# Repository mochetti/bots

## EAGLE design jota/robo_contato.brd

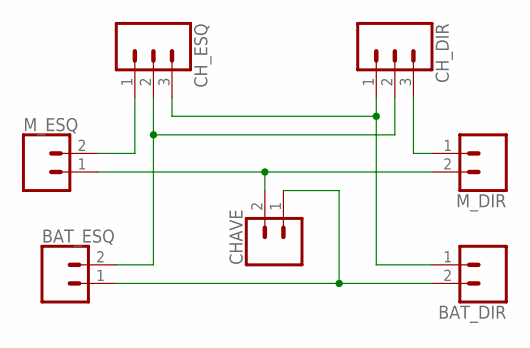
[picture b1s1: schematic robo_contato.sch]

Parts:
BAT_DIR: CONN_02; 1X02
BAT_ESQ: CONN_02; 1X02
CHAVE: CONN_02; 1X02
CH_DIR: CONN_03; 1X03
CH_ESQ: CONN_03; 1X03
M_DIR: CONN_02; 1X02
M_ESQ: CONN_02; 1X02

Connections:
unnamed: BAT_ESQ.2, CH_DIR.2, CH_ESQ.2
unnamed: CHAVE.2, M_DIR.2, M_ESQ.1
unnamed: BAT_DIR.1, CH_DIR.1, CH_ESQ.3
unnamed: CH_DIR.3, M_DIR.1
unnamed: CH_ESQ.1, M_ESQ.2
unnamed: BAT_DIR.2, BAT_ESQ.1, CHAVE.1

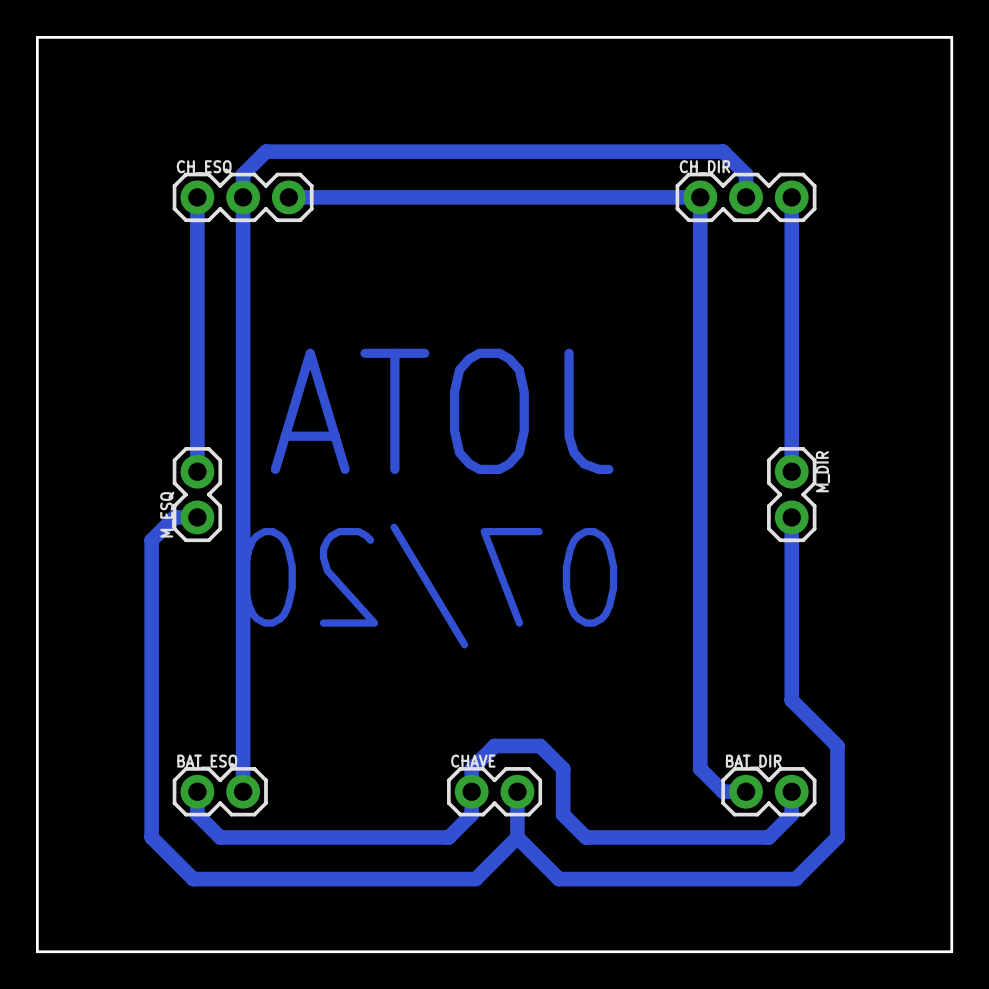
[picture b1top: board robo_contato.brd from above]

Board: 2 copper layers, 50.8 x 50.8 mm, 7 parts (0 on the bottom side), 6 nets.

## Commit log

2020-07-27 placa do jota

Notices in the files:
parts and their libraries:
SparkFun-Connectors: Licensing: Creative Commons ShareAlike 4.0 International - https://creativecommons.org/licenses/by-sa/4.0
